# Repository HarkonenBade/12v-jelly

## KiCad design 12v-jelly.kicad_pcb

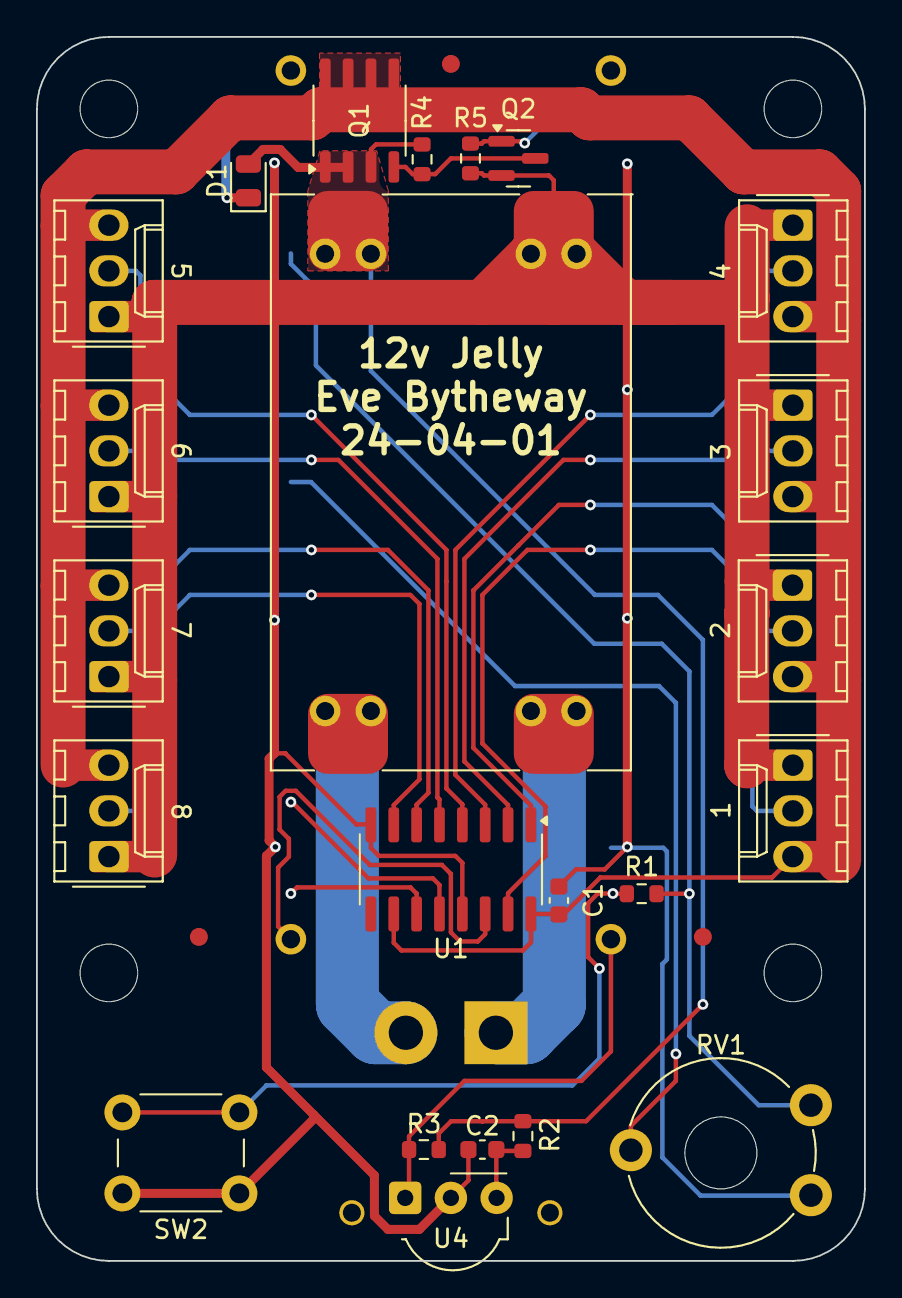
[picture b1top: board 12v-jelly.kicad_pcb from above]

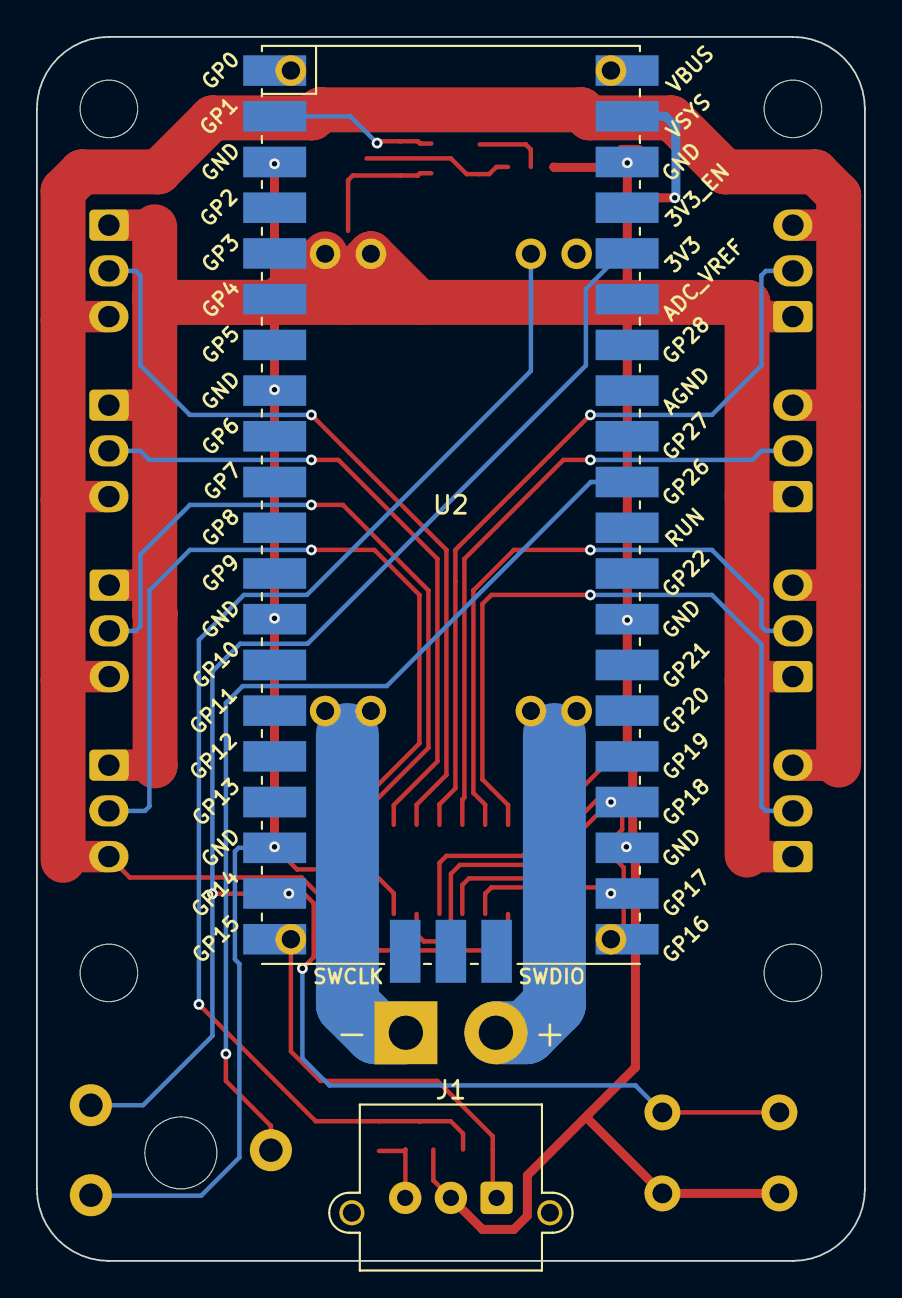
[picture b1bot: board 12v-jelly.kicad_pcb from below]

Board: 2 copper layers, 46.0 x 68.0 mm, 32 parts (2 on the bottom side), 24 nets.

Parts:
C1, C2: 100n; C_0603_1608Metric
D1: D_Small; D_0805_2012Metric
FID1, FID2, FID3: Fiducial; Fiducial_1mm_Mask2mm
H1, H2, H3, H4: MountingHole; MountingHole_3.2mm_M3
J1: PWR; AMASS_XT30PW-M_1x02_P2.50mm_Horizontal
J3: 1; Molex_KK-254_AE-6410-03A_1x03_P2.54mm_Vertical
J4: 2; Molex_KK-254_AE-6410-03A_1x03_P2.54mm_Vertical
J5: 3; Molex_KK-254_AE-6410-03A_1x03_P2.54mm_Vertical
J6: 4; Molex_KK-254_AE-6410-03A_1x03_P2.54mm_Vertical
J7: 5; Molex_KK-254_AE-6410-03A_1x03_P2.54mm_Vertical
J8: 6; Molex_KK-254_AE-6410-03A_1x03_P2.54mm_Vertical
J9: 7; Molex_KK-254_AE-6410-03A_1x03_P2.54mm_Vertical
J10: 8; Molex_KK-254_AE-6410-03A_1x03_P2.54mm_Vertical
Q1: DMP2022LSS-13; SO-8_3.9x4.9mm_P1.27mm
Q2: 2N7002; SOT-23
R1, R4, R5: 10k; R_0603_1608Metric
R2: 100r; R_0603_1608Metric
R3: 20k; R_0603_1608Metric
RV1: 100k; Potentiometer_Piher_PT-10-V10_Vertical_Hole
SW2: SW_Push; SW_PUSH_6mm_H13mm
U1: 74HC595; SOIC-16_3.9x9.9mm_P1.27mm
U2: RPi Pico; RPi_Pico_SMD
U3: Mini560; mini560
U4: VS1838B; Vishay_MOLD-3Pin

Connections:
+3V3: R1.1, RV1.1, U2.36 (3V3)
+5V: D1.2 (A), Q1.1 (S), Q1.2 (S), Q1.3 (S), R2.2, R3.2, R4.1, U3.3 (OUT+)
/CLOCK: U1.11 (SRCLK), U2.22 (GPIO17)
/DATA: U1.14 (SER), U2.21 (GPIO16)
/IR: R3.1, U2.20 (GPIO15), U4.1 (OUT)
/LATCH: U1.12 (RCLK), U2.24 (GPIO18)
/LED_EN: Q2.1 (G), R5.1, U2.2 (GPIO1)
/POT: RV1.2, U2.31 (GPIO26_ADC0)
/SW0: R1.2, SW2.2, U2.19 (GPIO14)
GND: C1.2, C2.2, J3.1, J4.1, J5.1, J6.1, J7.1, J8.1, J9.1, J10.1, Q2.2 (S), R5.2, RV1.3, SW2.1, U1.8 (GND), U1.13 (~OE), U2.3 (GND), U2.8 (GND), U2.13 (GND), U2.18 (GND), U2.23 (GND), U2.28 (GND), U2.38 (GND), U3.4 (OUT-), U4.2 (GND)
LED_PWR: C1.1, J3.3, J4.3, J5.3, J6.3, J7.3, J8.3, J9.3, J10.3, Q1.5 (D), Q1.6 (D), Q1.7 (D), Q1.8 (D), U1.10 (~SRCLR), U1.16 (VCC)
unnamed: D1.1 (K), U2.39 (VSYS)
unnamed: J1.1, U3.2 (IN-)
unnamed: J1.2, U3.1 (IN+)
unnamed: J3.2, U1.15 (QA)
unnamed: J4.2, U1.1 (QB)
unnamed: J5.2, U1.2 (QC)
unnamed: J6.2, U1.3 (QD)
unnamed: J7.2, U1.4 (QE)
unnamed: J8.2, U1.5 (QF)
unnamed: J9.2, U1.6 (QG)
unnamed: J10.2, U1.7 (QH)
unnamed: Q1.4 (G), Q2.3 (D), R4.2
unnamed: C2.1, R2.1, U4.3 (Vs)

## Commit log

2023-11-10 12v Jelly base schematic and layout
2023-11-16 Tweaks Tweaks Tweaks
2023-11-19 Double Sided layout and further tweaks
2023-11-19 Minor tweaks and ibom
2023-11-19 gerbers v1
2023-11-23 More tweaks
2023-11-24 More bits
2023-11-24 Tiny tweaks
2023-11-24 Number old gerbers
2023-11-24 New Gerbers 0.2
2024-04-01 MOSFET
2024-04-03 PMOS not NMOS
2024-04-04 Driver NMOS
2024-04-04 Oh gods the wires
2024-04-04 More routing tweaks, and DRC fixes.
2024-04-05 Part numbers
2024-04-05 Gerbers v0.3
